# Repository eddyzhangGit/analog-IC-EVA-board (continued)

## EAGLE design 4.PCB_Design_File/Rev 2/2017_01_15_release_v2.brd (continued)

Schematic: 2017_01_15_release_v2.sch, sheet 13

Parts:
C19: 22u; C0805
C43, C156, C159, C265: 10u; C0805
C48: 3.3n; C0603
C157, C162, C264, C267, C268, C269, C270: 0.1u; C0603
C266: 2.2n; C0603
C273: 4.7u; C0805
R2, R103: 0; R0603
R3: 0.68; R1206
R38, R39: 100; R0603
R40: 10k; R0603
R41: 1800; R0603
R73: 500; R0603
SV2: MA03-1
TP21, TP22: TPSQTP20R; TP20R
U$4: AD5248; MSOP10
U$6: LP38511_SOIC; SOIC_8N_PAD
U$21: MAX44284; SOT23-6

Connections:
3V3: C43.1, C156.1, C157.1, C264.1, C265.1, C270.1, C273.1, R40.2, U$4.5 (VDD1), U$6.7 (IN2), U$6.8 (IN1), U$21.1 (VDD), U$21.6 (SHDN); also elsewhere on the board
A0: C266.1, R41.1, TP22.TP; also elsewhere on the board
A1: R2.2, TP21.TP; also elsewhere on the board
EN1: R40.1, U$6.6 (EN); also elsewhere on the board
GND: C19.2, C43.2, C156.2, C157.2, C159.2, C162.2, C264.2, C265.2, C266.2, C268.1, C269.2, C270.2, C273.2, R73.2, SV2.3, U$4.2 (A0), U$4.3 (W2), U$4.4 (GND1), U$4.8 (A1), U$6.5 (GND), U$6.9 (DAP), U$21.2 (GND); also elsewhere on the board
N123~1: R41.2, U$21.5 (SENSE_OUT)
unnamed: C48.2, R73.1, R103.1, U$4.10 (W1), U$6.3 (ADJ)
unnamed: C267.2, C269.1, R39.1, U$21.3 (RS+)
unnamed: R103.2, U$4.9 (B2)
unnamed: C267.1, C268.2, R38.1, U$21.4 (RS-)
P6.4_I2C1_SDA: U$4.7 (SDA); also elsewhere on the board
P6.5_I2C1_SCL: U$4.6 (SCL); also elsewhere on the board
VOUT1: R2.1, R3.1, R38.2, SV2.1; also elsewhere on the board
VOUT1_RS: C19.1, C48.1, C159.1, C162.1, R3.2, R39.2, U$4.1 (B1), U$6.1 (OUT1), U$6.2 (OUT2)

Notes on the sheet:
ADJ power supply (1/6) (50mA x 4)
Input_Filtering
Output_Filtering
High Side Current Sensing
i2c Address : 58
NOTE : R103 should be left open
0.68_Ohm * 50mA * gain_100
MAX44284H_100x_gain
Vout = (1 + R_POT/500) * 0.5V
AD5248BRMZ2.5
LP38511MR-ADJ/NOPB

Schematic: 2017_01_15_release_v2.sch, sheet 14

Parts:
ADJ2: LP38511_SOIC; SOIC_8N_PAD
C46: 3.3n; C0603K
C51, C52, C59, C146: 10u; C0805
C53: 22u; C0805
C55, C57, C145, C148, C274, C275, C276: 0.1u; C0603
C147: 2.2n; C0603
C279: 4.7u; C0805
POT2: AD5248; MSOP10
R4: 0.68; R1206
R42: 10k; R0603
R43, R44: 100; R0603
R45: 1800; R0603
R54, R104: 0; R0603
R84: 500; R0603
SV4: MA03-1
TP23, TP24: TPSQTP20R; TP20R
VSEN2: MAX44284; SOT23-6

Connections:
3V3: ADJ2.7 (IN2), ADJ2.8 (IN1), C51.1, C52.1, C55.1, C145.1, C146.1, C276.1, C279.1, POT2.2 (A0), POT2.5 (VDD1), R42.2, VSEN2.1 (VDD), VSEN2.6 (SHDN); also elsewhere on the board
A2: C147.1, R45.1, TP24.TP; also elsewhere on the board
A3: R54.2, TP23.TP; also elsewhere on the board
EN2: ADJ2.6 (EN), R42.1; also elsewhere on the board
GND: ADJ2.5 (GND), ADJ2.9 (DAP), C51.2, C52.2, C53.2, C55.2, C57.2, C59.2, C145.2, C146.2, C147.2, C274.1, C275.2, C276.2, C279.2, POT2.3 (W2), POT2.4 (GND1), POT2.8 (A1), R84.2, SV4.3, VSEN2.2 (GND); also elsewhere on the board
N123~2: R45.2, VSEN2.5 (SENSE_OUT)
unnamed: C148.2, C275.1, R44.1, VSEN2.3 (RS+)
unnamed: C148.1, C274.2, R43.1, VSEN2.4 (RS-)
unnamed: POT2.9 (B2), R104.2
unnamed: ADJ2.3 (ADJ), C46.2, POT2.10 (W1), R84.1, R104.1
P6.4_I2C1_SDA: POT2.7 (SDA); also elsewhere on the board
P6.5_I2C1_SCL: POT2.6 (SCL); also elsewhere on the board
VOUT2: R4.1, R43.2, R54.1, SV4.1; also elsewhere on the board
VOUT2_RS: ADJ2.1 (OUT1), ADJ2.2 (OUT2), C46.1, C53.1, C57.1, C59.1, POT2.1 (B1), R4.2, R44.2

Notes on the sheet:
ADJ power supply (2/6) (50mA x 4)
Input_Filtering
Output_Filtering
High Side Current Sensing
i2c Address : 5A
NOTE : R104 should be left open
0.68_Ohm * 50mA * gain_100
MAX44284H_100x_gain
Vout = (1 + R_POT/500) * 0.5V
AD5248BRMZ2.5
LP38511MR-ADJ/NOPB

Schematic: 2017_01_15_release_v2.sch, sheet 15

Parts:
ADJ3: LP38511_SOIC; SOIC_8N_PAD
C45, C70, C168: 10u; C0805
C47: 22u; C0805
C60: 3.3n; C0603K
C164, C170, C283, C284, C285, C286: 0.1u; C0603
C280: 0.1u; C0603K
C281: 10u; C0805K
C282: 2.2n; C0603
C289: 4.7u; C0805
POT3: AD5248; MSOP10
R46: 10k; R0603
R47, R48: 100; R0603
R53: 1800; R0603
R60, R105: 0; R0603
R68: 0.68; R1206
R87: 500; R0603
SV13: MA03-1
TP25, TP26: TPSQTP20R; TP20R
VSEN3: MAX44284; SOT23-6

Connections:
3V3: ADJ3.7 (IN2), ADJ3.8 (IN1), C45.1, C70.1, C164.1, C280.1, C281.1, C286.1, C289.1, POT3.5 (VDD1), POT3.8 (A1), R46.2, VSEN3.1 (VDD), VSEN3.6 (SHDN); also elsewhere on the board
A4: C282.1, R53.1, TP26.TP; also elsewhere on the board
A5: R60.1, TP25.TP; also elsewhere on the board
EN3: ADJ3.6 (EN), R46.1; also elsewhere on the board
GND: ADJ3.5 (GND), ADJ3.9 (DAP), C45.2, C47.2, C70.2, C164.2, C168.2, C170.2, C280.2, C281.2, C282.2, C284.1, C285.2, C286.2, C289.2, POT3.2 (A0), POT3.3 (W2), POT3.4 (GND1), R87.2, SV13.3, VSEN3.2 (GND); also elsewhere on the board
N123~3: R53.2, VSEN3.5 (SENSE_OUT)
unnamed: C283.1, C284.2, R47.1, VSEN3.4 (RS-)
unnamed: POT3.9 (B2), R105.2
unnamed: C283.2, C285.1, R48.1, VSEN3.3 (RS+)
unnamed: ADJ3.3 (ADJ), C60.2, POT3.10 (W1), R87.1, R105.1
P6.4_I2C1_SDA: POT3.7 (SDA); also elsewhere on the board
P6.5_I2C1_SCL: POT3.6 (SCL); also elsewhere on the board
VOUT3: R47.2, R60.2, R68.1, SV13.1; also elsewhere on the board
VOUT3_RS: ADJ3.1 (OUT1), ADJ3.2 (OUT2), C47.1, C60.1, C168.1, C170.1, POT3.1 (B1), R48.2, R68.2

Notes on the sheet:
ADJ power supply (3/6) (50mA x 4)
Input_Filtering
Output_Filtering
High Side Current Sensing
i2c Address : 5c
NOTE : R105 should be left open
0.68_Ohm * 50mA * gain_100
MAX44284H_100x_gain
Vout = (1 + R_POT/500) * 0.5V
AD5248BRMZ2.5
LP38511MR-ADJ/NOPB

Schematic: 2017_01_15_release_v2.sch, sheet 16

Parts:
ADJ4: LP38511_SOIC; SOIC_8N_PAD
C54, C71, C76, C81: 10u; C0805
C56: 22u; C0805
C64: 3.3n; C0603K
C72, C78, C80, C83, C84, C85: 0.1u; C0603
C82: 2.2n; C0603
C86: 0.1u; C0603K
C174: 4.7u; C0805K
POT4: AD5248; MSOP10
R49: 10k; R0603
R50, R51: 100; R0603
R52: 1800; R0603
R55: 0.68; R1206
R92: 500; R0603
R128, R190: 0; R0603
SV14: MA03-1
TP27, TP28: TPSQTP20R; TP20R
VSEN4: MAX44284; SOT23-6

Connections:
3V3: ADJ4.7 (IN2), ADJ4.8 (IN1), C54.1, C71.1, C72.1, C80.1, C81.1, C86.1, C174.1, POT4.2 (A0), POT4.5 (VDD1), POT4.8 (A1), R49.2, VSEN4.1 (VDD), VSEN4.6 (SHDN); also elsewhere on the board
A6: C82.1, R52.1, TP28.TP; also elsewhere on the board
A7: R128.1, TP27.TP; also elsewhere on the board
EN4: ADJ4.6 (EN), R49.1; also elsewhere on the board
GND: ADJ4.5 (GND), ADJ4.9 (DAP), C54.2, C56.2, C71.2, C72.2, C76.2, C78.2, C80.2, C81.2, C82.2, C84.1, C85.2, C86.2, C174.2, POT4.3 (W2), POT4.4 (GND1), R92.2, SV14.3, VSEN4.2 (GND); also elsewhere on the board
N123~4: R52.2, VSEN4.5 (SENSE_OUT)
unnamed: POT4.9 (B2), R190.2
unnamed: C83.2, C85.1, R51.1, VSEN4.3 (RS+)
unnamed: C83.1, C84.2, R50.1, VSEN4.4 (RS-)
unnamed: ADJ4.3 (ADJ), C64.2, POT4.10 (W1), R92.1, R190.1
P6.4_I2C1_SDA: POT4.7 (SDA); also elsewhere on the board
P6.5_I2C1_SCL: POT4.6 (SCL); also elsewhere on the board
VOUT4: R50.2, R55.1, R128.2, SV14.1; also elsewhere on the board
VOUT4_RS: ADJ4.1 (OUT1), ADJ4.2 (OUT2), C56.1, C64.1, C76.1, C78.1, POT4.1 (B1), R51.2, R55.2

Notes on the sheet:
ADJ power supply (4/6) (50mA x 4)
Input_Filtering
Output_Filtering
High Side Current Sensing
i2c Address : 5E
NOTE : R190 should be left open
0.68_Ohm * 50mA * gain_100
MAX44284H_100x_gain
Vout = (1 + R_POT/500) * 0.5V
AD5248BRMZ2.5
LP38511MR-ADJ/NOPB

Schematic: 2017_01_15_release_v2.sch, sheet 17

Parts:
ADJ5: LP38511_SOIC; SOIC_8N_PAD
C58, C140, C292, C297: 10u; C0805
C61: 22u; C0805
C88: 3.3n; C0603K
C141, C294, C296, C299, C300, C301, C302: 0.1u; C0603
C298: 2.2n; C0603
C305: 4.7u; C0805
POT5: AD5248; MSOP10
R56: 10k; R0603
R57, R58: 100; R0603
R59: 1800; R0603
R61: 0.16; R1206
R69, R108: 0; R0603
R98: 500; R0603
SV15: MA03-1
TP29, TP30: TPSQTP20R; TP20R
VSEN5: MAX44284; SOT23-6

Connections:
3V3: ADJ5.7 (IN2), ADJ5.8 (IN1), C58.1, C140.1, C141.1, C296.1, C297.1, C302.1, C305.1, POT5.5 (VDD1), R56.2, VSEN5.1 (VDD), VSEN5.6 (SHDN); also elsewhere on the board
A8: C298.1, R59.1, TP30.TP; also elsewhere on the board
A12: R69.1, TP29.TP; also elsewhere on the board
EN5: ADJ5.6 (EN), R56.1; also elsewhere on the board
GND: ADJ5.5 (GND), ADJ5.9 (DAP), C58.2, C61.2, C140.2, C141.2, C292.2, C294.2, C296.2, C297.2, C298.2, C300.1, C301.2, C302.2, C305.2, POT5.2 (A0), POT5.3 (W2), POT5.4 (GND1), POT5.8 (A1), R98.2, SV15.3, VSEN5.2 (GND); also elsewhere on the board
N123~5: R59.2, VSEN5.5 (SENSE_OUT)
unnamed: C299.1, C300.2, R57.1, VSEN5.4 (RS-)
unnamed: POT5.9 (B2), R108.2
unnamed: C299.2, C301.1, R58.1, VSEN5.3 (RS+)
unnamed: ADJ5.3 (ADJ), C88.2, POT5.10 (W1), R98.1, R108.1
P3.6_I2C2_SDA: POT5.7 (SDA); also elsewhere on the board
P3.7_I2C2_SCL: POT5.6 (SCL); also elsewhere on the board
VOUT5: R57.2, R61.1, R69.2, SV15.1; also elsewhere on the board
VOUT5_RS: ADJ5.1 (OUT1), ADJ5.2 (OUT2), C61.1, C88.1, C292.1, C294.1, POT5.1 (B1), R58.2, R61.2

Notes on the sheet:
ADJ power supply (5/6) (200mA x 2)
Input_Filtering
Output_Filtering
High Side Current Sensing
i2c Address : 58
NOTE : R108 should be left open
0.16_Ohm * 200mA * gain_100
MAX44284H_100x_gain
Vout = (1 + R_POT/500) * 0.5V
LP38511MR-ADJ/NOPB

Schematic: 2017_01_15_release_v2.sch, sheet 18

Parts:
ADJ6: LP38511_SOIC; SOIC_8N_PAD
C62, C310, C315, C320: 10u; C0805
C63: 22u; C0805
C306: 3.3n; C0603K
C311, C317, C319, C322, C323, C325: 0.1u; C0603
C321: 2.2n; C0603
C324: 0.1u; C0603K
C328: 4.7u; C0805
POT6: AD5248; MSOP10
R62: 10k; R0603
R63, R64: 100; R0603
R65: 1800; R0603
R66: 0.16; R1206
R71, R109: 0; R0603
R101: 500; R0603
SV16: MA03-1
TP31, TP32: TPSQTP20R; TP20R
VSEN6: MAX44284; SOT23-6

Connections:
3V3: ADJ6.7 (IN2), ADJ6.8 (IN1), C62.1, C310.1, C311.1, C319.1, C320.1, C325.1, C328.1, POT6.2 (A0), POT6.5 (VDD1), R62.2, VSEN6.1 (VDD), VSEN6.6 (SHDN); also elsewhere on the board
A13: C321.1, R65.1, TP32.TP; also elsewhere on the board
A14: R71.2, TP31.TP; also elsewhere on the board
EN6: ADJ6.6 (EN), R62.1; also elsewhere on the board
GND: ADJ6.5 (GND), ADJ6.9 (DAP), C62.2, C63.2, C310.2, C311.2, C315.2, C317.2, C319.2, C320.2, C321.2, C323.1, C324.2, C325.2, C328.2, POT6.3 (W2), POT6.4 (GND1), POT6.8 (A1), R101.2, SV16.3, VSEN6.2 (GND); also elsewhere on the board
N123~6: R65.2, VSEN6.5 (SENSE_OUT)
unnamed: POT6.9 (B2), R109.2
unnamed: C322.2, C324.1, R64.1, VSEN6.3 (RS+)
unnamed: C322.1, C323.2, R63.1, VSEN6.4 (RS-)
unnamed: ADJ6.3 (ADJ), C306.2, POT6.10 (W1), R101.1, R109.1
P3.6_I2C2_SDA: POT6.7 (SDA); also elsewhere on the board
P3.7_I2C2_SCL: POT6.6 (SCL); also elsewhere on the board
VOUT6: R63.2, R66.1, R71.1, SV16.1; also elsewhere on the board
VOUT6_RS: ADJ6.1 (OUT1), ADJ6.2 (OUT2), C63.1, C306.1, C315.1, C317.1, POT6.1 (B1), R64.2, R66.2

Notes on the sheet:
ADJ power supply (6/6) (200mA x 2)
Input_Filtering
Output_Filtering
High Side Current Sensing
i2c Address : 5A
NOTE : R109 should be left open
0.16_Ohm * 200mA * gain_100
MAX44284H_100x_gain
Vout = (1 + R_POT/500) * 0.5V
AD5248BRMZ2.5
LP38511MR-ADJ/NOPB

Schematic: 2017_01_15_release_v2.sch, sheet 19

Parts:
C66, C67, C68, C69, C75, C77, C79, C93, C330, C336, C342: 0.1u; C0603
C329: 3.3n; C0603K
C331, C333, C340: 10u; C0805
R70, R106, R107, R138, R139: 10k; R0603
R72: 0; R0805
R102: 500; R0603
R110, R111, R112, R113, R114, R115, R116, R117, R118, R119, R120, R123, R124, R125, R126, R127: 5k; R0603
TP42: TPSQTP20R; TP20R
U$9, U$10, U$22, U$23: TXB0304; UQFN-12(RUT-12)
U$24: LP38511_SOIC; SOIC_8N_PAD
U$31: AD5248; MSOP10

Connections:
3V3: C66.2, C67.2, C68.2, C69.2, C330.1, C331.1, C333.1, C336.1, R70.2, R106.1, R107.1, R110.1, R111.1, R112.1, R113.1, R114.1, R115.1, R116.1, R117.1, R118.1, R119.1, R120.1, R123.1, R124.1, R125.1, R126.1, R127.1, R138.1, R139.1, U$9.OE, U$9.VCCA, U$10.OE, U$10.VCCA, U$22.OE, U$22.VCCA, U$23.OE, U$23.VCCA, U$24.7 (IN2), U$24.8 (IN1), U$31.5 (VDD1), U$31.8 (A1); also elsewhere on the board
A15: R72.1; also elsewhere on the board
EN7: R70.1, U$24.6 (EN); also elsewhere on the board
GND: C66.1, C67.1, C68.1, C69.1, C75.1, C77.1, C79.1, C93.1, C330.2, C331.2, C333.2, C336.2, C340.2, C342.2, R102.2, R106.2, R107.2, R138.2, R139.2, U$9.GND, U$10.GND, U$22.GND, U$23.GND, U$24.5 (GND), U$24.9 (DAP), U$31.2 (A0), U$31.4 (GND1); also elsewhere on the board
GPIO1: R110.2, U$9.A4; also elsewhere on the board
GPIO2: R111.2, U$9.A3; also elsewhere on the board
GPIO3: R112.2, U$9.A2; also elsewhere on the board
GPIO4: R113.2, U$9.A1; also elsewhere on the board
GPIO5: R114.2, U$10.A4; also elsewhere on the board
GPIO6: R115.2, U$10.A3; also elsewhere on the board
GPIO7: R116.2, U$10.A2; also elsewhere on the board
GPIO8: R117.2, U$10.A1; also elsewhere on the board
GPIO9: R118.2, U$22.A4; also elsewhere on the board
GPIO10: R119.2, U$22.A3; also elsewhere on the board
GPIO11: R120.2, U$22.A2; also elsewhere on the board
GPIO12: R123.2, U$22.A1; also elsewhere on the board
GPIO13: R124.2, U$23.A4; also elsewhere on the board
GPIO14: R125.2, U$23.A3; also elsewhere on the board
GPIO15: R126.2, U$23.A2; also elsewhere on the board
GPIO16: R127.2, U$23.A1; also elsewhere on the board
GPIO_OUT1: U$9.B4; also elsewhere on the board
GPIO_OUT2: U$9.B3; also elsewhere on the board
GPIO_OUT3: U$9.B2; also elsewhere on the board
GPIO_OUT4: U$9.B1; also elsewhere on the board
GPIO_OUT5: U$10.B4; also elsewhere on the board
GPIO_OUT6: U$10.B3; also elsewhere on the board
GPIO_OUT7: U$10.B2; also elsewhere on the board
GPIO_OUT8: U$10.B1; also elsewhere on the board
GPIO_OUT9: U$22.B4; also elsewhere on the board
GPIO_OUT10: U$22.B3; also elsewhere on the board
GPIO_OUT11: U$22.B2; also elsewhere on the board
GPIO_OUT12: U$22.B1; also elsewhere on the board
GPIO_OUT13: U$23.B4; also elsewhere on the board
GPIO_OUT14: U$23.B3; also elsewhere on the board
GPIO_OUT15: U$23.B2; also elsewhere on the board
GPIO_OUT16: U$23.B1; also elsewhere on the board
unnamed: C329.2, R102.1, U$24.3 (ADJ), U$31.10 (W1)
P3.6_I2C2_SDA: U$31.7 (SDA); also elsewhere on the board
P3.7_I2C2_SCL: U$31.6 (SCL); also elsewhere on the board
POT2K5_B: U$31.9 (B2); also elsewhere on the board
POT2K5_W: U$31.3 (W2); also elsewhere on the board
V_IO: C75.2, C77.2, C79.2, C93.2, C329.1, C340.1, C342.1, R72.2, TP42.TP, U$9.VCCB, U$10.VCCB, U$22.VCCB, U$23.VCCB, U$24.1 (OUT1), U$24.2 (OUT2), U$31.1 (B1)

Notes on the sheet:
Digital IOs
Input_Filtering
Output_Filtering
i2c Address : 5C
AD5248BRMZ2.5
TXB0304RUTR
LP38511MR-ADJ/NOPB

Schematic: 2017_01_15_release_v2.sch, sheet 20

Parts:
C223: 0.1u; C0603
C224: 10u; C0805
U$13: AD5248; MSOP10

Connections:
3V3: C223.1, C224.1, U$13.2 (A0), U$13.5 (VDD1), U$13.8 (A1); also elsewhere on the board
GND: C223.2, C224.2, U$13.4 (GND1); also elsewhere on the board
P3.6_I2C2_SDA: U$13.7 (SDA); also elsewhere on the board
P3.7_I2C2_SCL: U$13.6 (SCL); also elsewhere on the board
POT10K_B: U$13.9 (B2); also elsewhere on the board
POT10K_W: U$13.3 (W2); also elsewhere on the board

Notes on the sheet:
DIGITAL POT
i2c Address : 5E

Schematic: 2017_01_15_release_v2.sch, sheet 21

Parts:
J1: TSW-128-07-L-D; SAMTEC_TSW-128-07-L-D

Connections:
-OUT2: J1.41; also elsewhere on the board
-OUT4: J1.42; also elsewhere on the board
GND: J1.1, J1.3, J1.5, J1.7, J1.9, J1.11, J1.13, J1.17, J1.19, J1.20, J1.39, J1.40, J1.43, J1.44, J1.49, J1.50, J1.55, J1.56; also elsewhere on the board
GPIO_OUT1: J1.37; also elsewhere on the board
GPIO_OUT2: J1.38; also elsewhere on the board
GPIO_OUT3: J1.35; also elsewhere on the board
GPIO_OUT4: J1.36; also elsewhere on the board
GPIO_OUT5: J1.33; also elsewhere on the board
GPIO_OUT6: J1.34; also elsewhere on the board
GPIO_OUT7: J1.31; also elsewhere on the board
GPIO_OUT8: J1.32; also elsewhere on the board
GPIO_OUT9: J1.29; also elsewhere on the board
GPIO_OUT10: J1.30; also elsewhere on the board
GPIO_OUT11: J1.27; also elsewhere on the board
GPIO_OUT12: J1.28; also elsewhere on the board
GPIO_OUT13: J1.25; also elsewhere on the board
GPIO_OUT14: J1.26; also elsewhere on the board
GPIO_OUT15: J1.23; also elsewhere on the board
GPIO_OUT16: J1.24; also elsewhere on the board
IOUT1: J1.52; also elsewhere on the board
IOUT2: J1.51; also elsewhere on the board
IOUT3: J1.54; also elsewhere on the board
IOUT4: J1.53; also elsewhere on the board
OUT1: J1.45; also elsewhere on the board
OUT2: J1.47; also elsewhere on the board
OUT3: J1.46; also elsewhere on the board
OUT4: J1.48; also elsewhere on the board
POT2K5_B: J1.21; also elsewhere on the board
POT2K5_W: J1.22; also elsewhere on the board
POT10K_B: J1.15; also elsewhere on the board
POT10K_W: J1.16; also elsewhere on the board
VOUT1: J1.18; also elsewhere on the board
VOUT2: J1.12; also elsewhere on the board
VOUT3: J1.14; also elsewhere on the board
VOUT4: J1.10; also elsewhere on the board
VOUT5: J1.6, J1.8; also elsewhere on the board
VOUT6: J1.2, J1.4; also elsewhere on the board

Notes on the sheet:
OUTPUT_HEADER

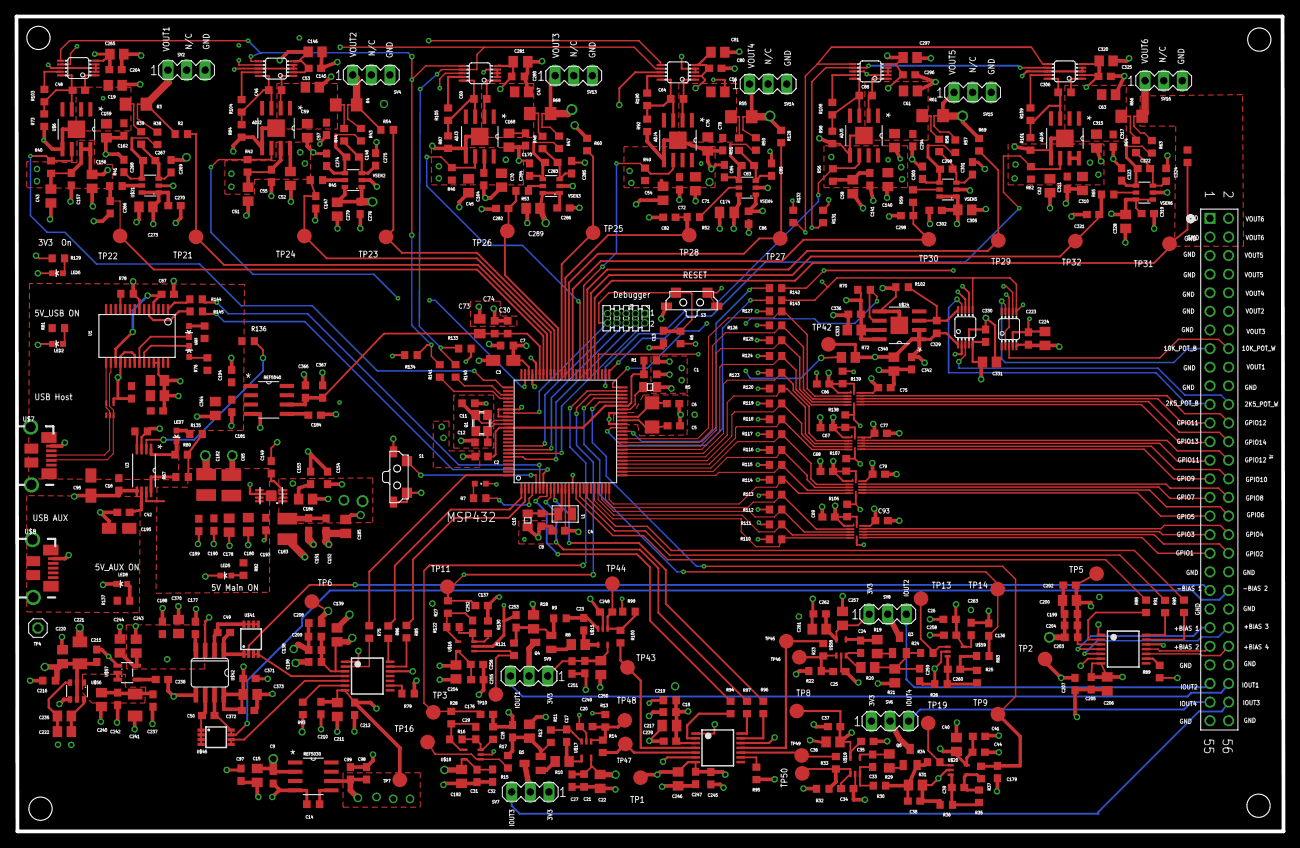
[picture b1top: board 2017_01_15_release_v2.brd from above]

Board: 4 copper layers, 173.0 x 111.3 mm, 511 parts (0 on the bottom side), 239 nets.

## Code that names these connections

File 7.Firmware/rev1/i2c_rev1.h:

/*
 * i2c_rev1.h
 *
 *  Created on: Nov 6, 2016
 *      Author: Maria
 */

#ifndef I2C_REV1_H_
#define I2C_REV1_H_

#define SLAVE_ADDRESS_1		0x58>>1		// A0 = GND, A1 = GND, (VOUT1, VOUT5)
#define SLAVE_ADDRESS_2		0x5A>>1		// A0 = 3V3, A1 = GND, (VOUT2, VOUT6)
#define SLAVE_ADDRESS_3		0x5C>>1		// A0 = GND, A1 = 3V3, (VOUT3, V_IO & POT2K5)
#define SLAVE_ADDRESS_4		0x5E>>1		// A0 = 3V3, A1 = 3V3, (VOUT4, POT10K)

void i2c_init (void);
void i2c_write_pot (uint8_t id, uint8_t channel, uint8_t value);
void i2c_write8 (uint8_t slaveAdr, uint8_t pointer, uint8_t writeByte);
void i2c_test (void);

#endif /* I2C_REV1_H_ */

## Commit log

2017-04-17 User Manual
2017-04-17 Design files
2017-04-17 image added
2017-04-17 image
